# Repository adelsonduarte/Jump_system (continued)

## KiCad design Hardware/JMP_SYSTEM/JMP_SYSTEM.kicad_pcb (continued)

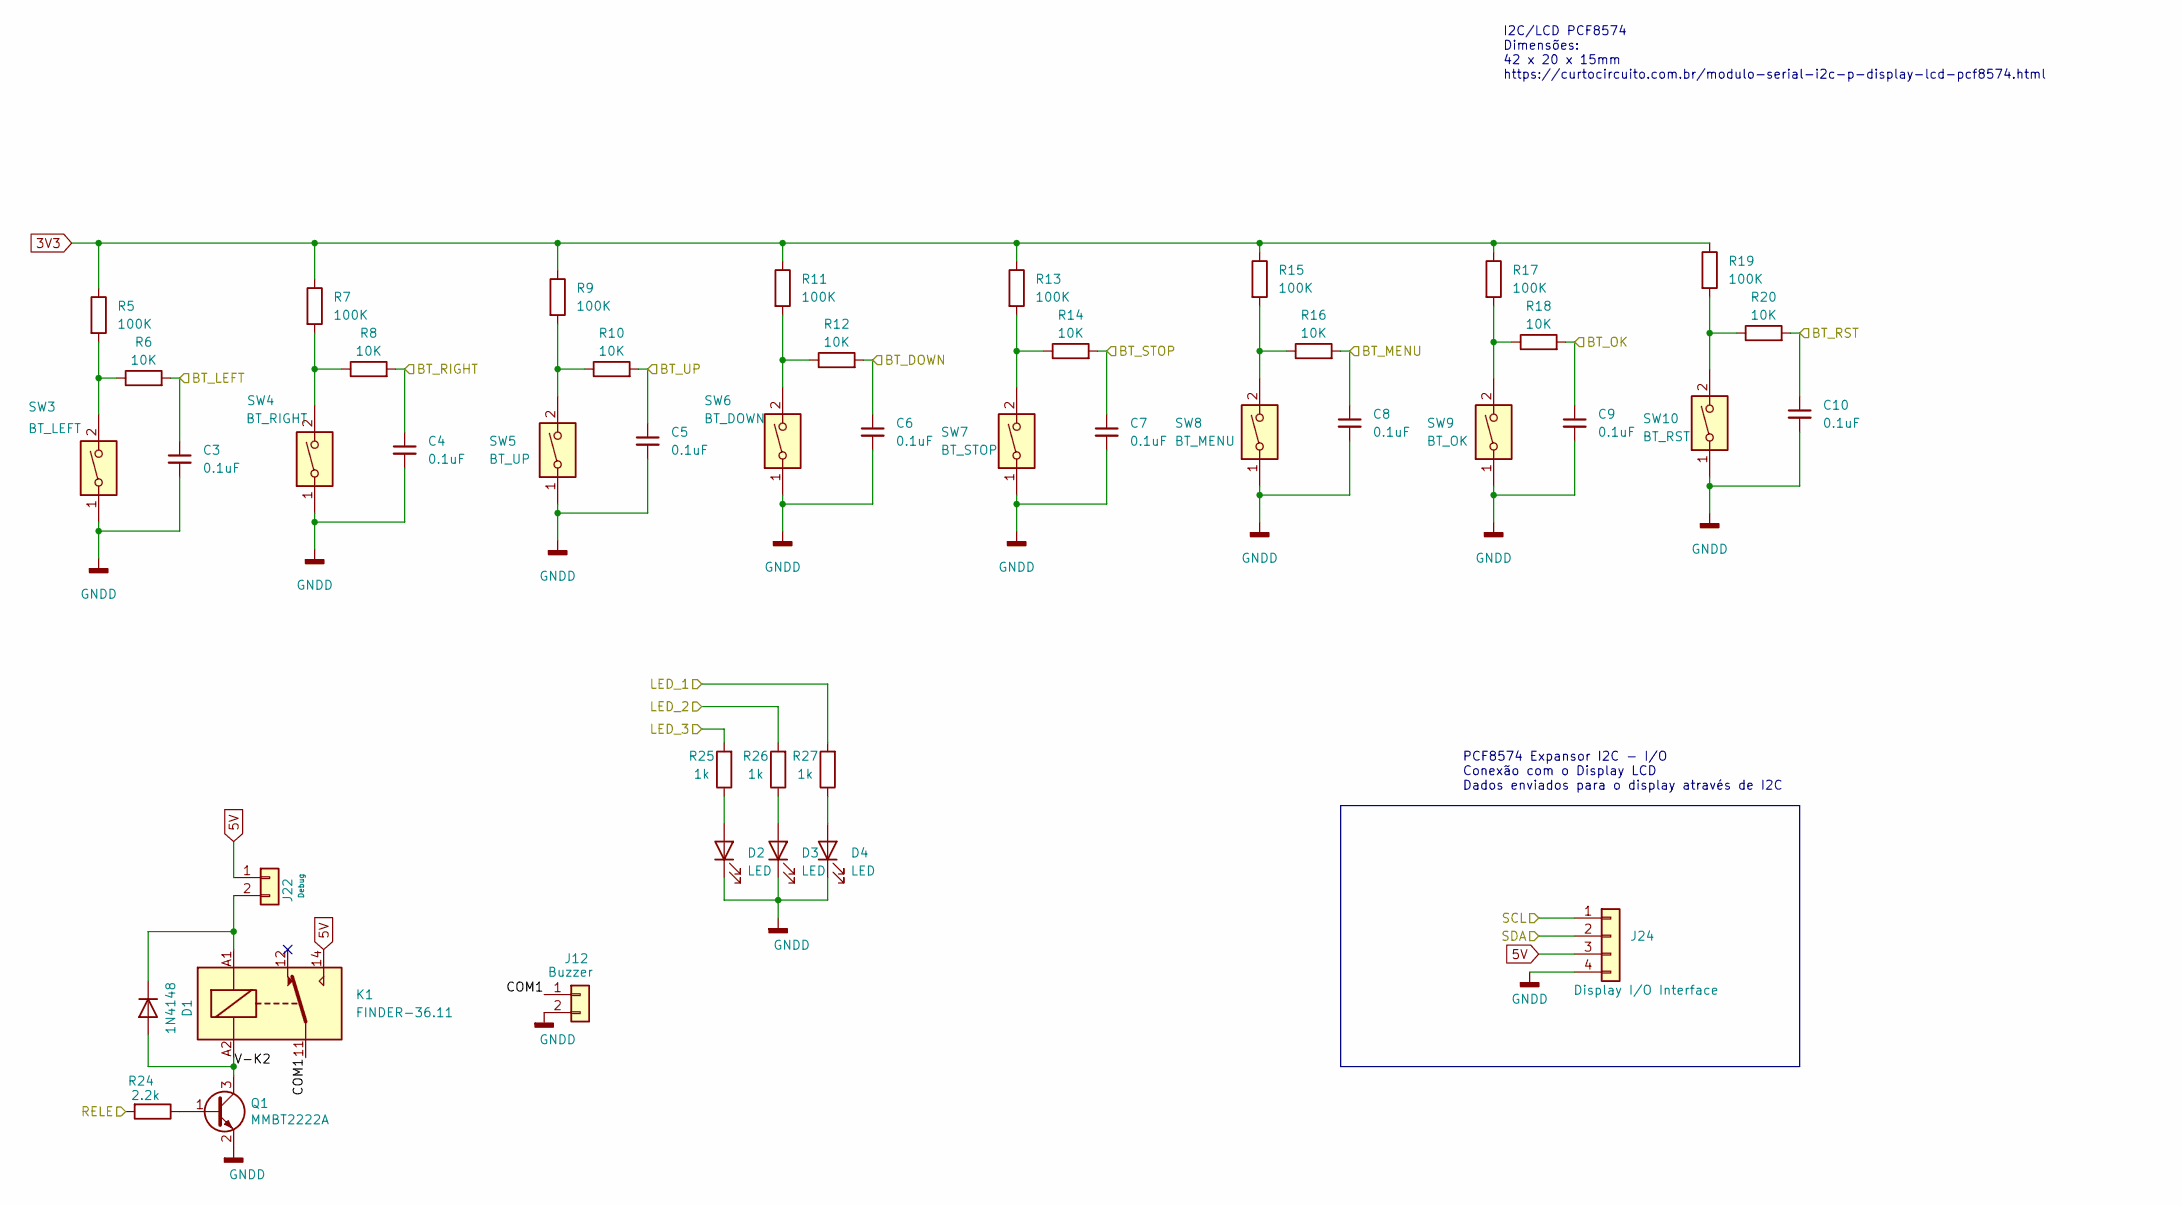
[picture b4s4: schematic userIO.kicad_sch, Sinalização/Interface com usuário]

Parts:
C3, C4, C5, C6, C7, C8, C9, C10: 0.1uF; R_0805_2012Metric_Pad1.20x1.40mm_HandSolder
D1: 1N4148; D_MiniMELF_Handsoldering
D2, D3, D4: LED; Molex_KK-254_AE-6410-02A_1x02_P2.54mm_Vertical
J12: Buzzer; Molex_KK-254_AE-6410-02A_1x02_P2.54mm_Vertical
J22: Debug; PinHeader_1x02_P2.54mm_Vertical
J24: Display I/O Interface; Molex_KK-254_AE-6410-04A_1x04_P2.54mm_Vertical
K1: FINDER-36.11; Relay_SPDT_Finder_36.11
Q1: MMBT2222A; SOT-23
R5, R7, R9, R11, R13, R15, R17, R19: 100K; R_0805_2012Metric_Pad1.20x1.40mm_HandSolder
R6, R8, R10, R12, R14, R16, R18, R20: 10K; R_0805_2012Metric_Pad1.20x1.40mm_HandSolder
R24: 2.2k; R_1206_3216Metric_Pad1.30x1.75mm_HandSolder
R25, R26, R27: 1k; R_0805_2012Metric_Pad1.20x1.40mm_HandSolder
SW3: BT_LEFT; Molex_KK-254_AE-6410-02A_1x02_P2.54mm_Vertical
SW4: BT_RIGHT; Molex_KK-254_AE-6410-02A_1x02_P2.54mm_Vertical
SW5: BT_UP; Molex_KK-254_AE-6410-02A_1x02_P2.54mm_Vertical
SW6: BT_DOWN; Molex_KK-254_AE-6410-02A_1x02_P2.54mm_Vertical
SW7: BT_STOP; Molex_KK-254_AE-6410-02A_1x02_P2.54mm_Vertical
SW8: BT_MENU; Molex_KK-254_AE-6410-02A_1x02_P2.54mm_Vertical
SW9: BT_OK; Molex_KK-254_AE-6410-02A_1x02_P2.54mm_Vertical
SW10: BT_RST; Molex_KK-254_AE-6410-02A_1x02_P2.54mm_Vertical

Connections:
3V3: R5.1, R7.1, R9.1, R11.1, R13.1, R15.1, R17.1, R19.1; also elsewhere on the board
5V: J22.1, J24.3, K1.14; also elsewhere on the board
/BT_DOWN: C6.1, R12.2; also elsewhere on the board
/BT_LEFT: C3.1, R6.2; also elsewhere on the board
/BT_MENU: C8.1, R16.2; also elsewhere on the board
/BT_OK: C9.1, R18.2; also elsewhere on the board
/BT_RIGHT: C4.1, R8.2; also elsewhere on the board
/BT_RST: C10.1, R20.2; also elsewhere on the board
/BT_STOP: C7.1, R14.2; also elsewhere on the board
/BT_UP: C5.1, R10.2; also elsewhere on the board
/LED_1: R27.2; also elsewhere on the board
/LED_2: R26.2; also elsewhere on the board
/LED_3: R25.2; also elsewhere on the board
/RELE: R24.2; also elsewhere on the board
/SCL: J24.1; also elsewhere on the board
/SDA: J24.2; also elsewhere on the board
/User _IO/COM1: J12.1, K1.11
/User _IO/V-K2: D1.2 (A), K1.A2, Q1.3 (C)
GNDA: C3.2, C4.2, C5.2, C6.2, C7.2, C8.2, C9.2, C10.2, D2.1 (K), D3.1 (K), D4.1 (K), J12.2, J24.4, Q1.2 (E), SW3.1, SW4.1, SW5.1, SW6.1, SW7.1, SW8.1, SW9.1, SW10.1; also elsewhere on the board
unnamed: D2.2 (A), R25.1
unnamed: D3.2 (A), R26.1
unnamed: D4.2 (A), R27.1
unnamed: D1.1 (K), J22.2, K1.A1
unnamed: Q1.1 (B), R24.1
unnamed: R5.2, R6.1, SW3.2
unnamed: R7.2, R8.1, SW4.2
unnamed: R9.2, R10.1, SW5.2
unnamed: R11.2, R12.1, SW6.2
unnamed: R13.2, R14.1, SW7.2
unnamed: R15.2, R16.1, SW8.2
unnamed: R17.2, R18.1, SW9.2
unnamed: R19.2, R20.1, SW10.2

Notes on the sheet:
PCF8574 Expansor I2C - I/O Conexão com o Display LCD Dados enviados para o display através de I2C
I2C/LCD PCF8574 Dimensões: 42 x 20 x 15mm https://curtocircuito.com.br/modulo-serial-i2c-p-display-lcd-pcf8574.html

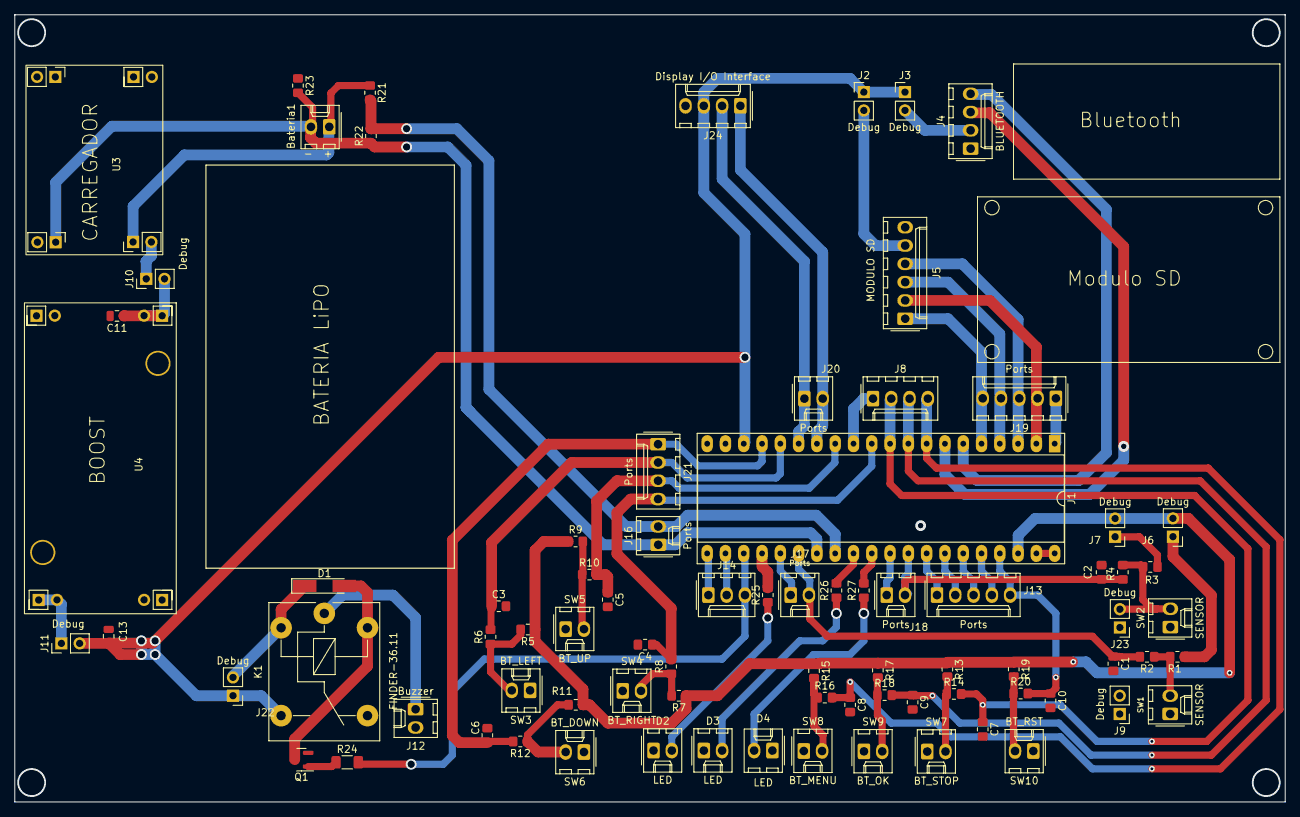
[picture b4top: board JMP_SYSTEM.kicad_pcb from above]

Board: 2 copper layers, 176.4 x 109.3 mm, 81 parts (0 on the bottom side), 60 nets.

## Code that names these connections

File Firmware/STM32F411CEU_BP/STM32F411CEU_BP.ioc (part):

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Mcu.Name=STM32F411C(C-E)Ux
Mcu.Package=UFQFPN48
Mcu.UserName=STM32F411CEUx
PA0-WKUP.Signal=S_TIM2_CH1_ETR
PA1.Signal=S_TIM2_CH2
PA10.GPIOParameters=GPIO_Label
PA10.GPIO_Label=LCD_D1
PA10.Signal=GPIO_Output
PA11.GPIOParameters=GPIO_Label
PA11.GPIO_Label=LCD_D0
PA11.Signal=GPIO_Output
PA12.GPIOParameters=GPIO_Label
PA12.GPIO_Label=LCD_EN
PA12.Signal=GPIO_Output
PA13.Mode=Serial_Wire
PA13.Signal=SYS_JTMS-SWDIO
PA14.Mode=Serial_Wire
PA14.Signal=SYS_JTCK-SWCLK
PA15.GPIOParameters=GPIO_Label
PA15.GPIO_Label=LCD_RW
PA15.Signal=GPIO_Output
PA2.Mode=Asynchronous
PA2.Signal=USART2_TX
PA3.Mode=Asynchronous
PA3.Signal=USART2_RX
PA4.GPIOParameters=GPIO_PuPd,GPIO_Label
PA4.GPIO_Label=SPI1_CS
PA4.GPIO_PuPd=GPIO_PULLUP
PA4.Signal=GPIO_Output
PA5.GPIOParameters=GPIO_PuPd
PA5.GPIO_PuPd=GPIO_PULLUP
PA5.Mode=Full_Duplex_Master
PA5.Signal=SPI1_SCK
PA6.GPIOParameters=GPIO_PuPd
PA6.GPIO_PuPd=GPIO_PULLUP
PA6.Mode=Full_Duplex_Master
PA6.Signal=SPI1_MISO
PA7.GPIOParameters=GPIO_PuPd
PA7.GPIO_PuPd=GPIO_PULLUP
PA7.Mode=Full_Duplex_Master
PA7.Signal=SPI1_MOSI
PA8.GPIOParameters=GPIO_Label
PA8.GPIO_Label=LCD_D3
PA8.Signal=GPIO_Output
PA9.GPIOParameters=GPIO_Label
PA9.GPIO_Label=LCD_D2
PA9.Signal=GPIO_Output
PB0.GPIOParameters=GPIO_PuPd,GPIO_Label,GPIO_ModeDefaultEXTI
PB0.GPIO_Label=BT_DOWN
PB0.GPIO_ModeDefaultEXTI=GPIO_MODE_IT_FALLING
PB0.GPIO_PuPd=GPIO_PULLUP
PB0.Signal=GPXTI0
PB1.GPIOParameters=GPIO_PuPd,GPIO_Label
PB1.GPIO_Label=BT_LEFT
PB1.GPIO_PuPd=GPIO_PULLUP
PB1.Signal=GPXTI1
PB12.GPIOParameters=GPIO_PuPd,GPIO_Label
PB12.GPIO_Label=LCD_D7
PB12.GPIO_PuPd=GPIO_NOPULL
PB12.Signal=GPIO_Output
PB13.GPIOParameters=GPIO_Label
PB13.GPIO_Label=LCD_D6
PB13.Signal=GPIO_Output
PB14.GPIOParameters=GPIO_Label
PB14.GPIO_Label=LCD_D5
PB14.Signal=GPIO_Output
PB15.GPIOParameters=GPIO_Label
PB15.GPIO_Label=LCD_D4
PB15.Signal=GPIO_Output
PB2.GPIOParameters=GPIO_PuPd,GPIO_Label
PB2.GPIO_Label=BT_ RIGHT
PB2.GPIO_PuPd=GPIO_PULLUP
PB2.Signal=GPXTI2
PB3.GPIOParameters=GPIO_Label
PB3.GPIO_Label=LCD_RS
PB3.Signal=GPIO_Output
PB4.GPIOParameters=GPIO_PuPd,GPIO_Label
PB4.GPIO_Label=BT_MENU
PB4.GPIO_PuPd=GPIO_PULLUP
PB4.Signal=GPXTI4
PB5.GPIOParameters=GPIO_PuPd,GPIO_Label,GPIO_ModeDefaultEXTI
PB5.GPIO_Label=BT_AVANCA
PB5.GPIO_ModeDefaultEXTI=GPIO_MODE_IT_FALLING
PB5.GPIO_PuPd=GPIO_PULLUP
PB5.Signal=GPXTI5
PB6.GPIOParameters=GPIO_PuPd,GPIO_Label,GPIO_ModeDefaultEXTI
PB6.GPIO_Label=BT_SELECT
PB6.GPIO_ModeDefaultEXTI=GPIO_MODE_IT_FALLING
PB6.GPIO_PuPd=GPIO_PULLUP
PB6.Signal=GPXTI6
PB7.GPIOParameters=GPIO_PuPd,GPIO_Label,GPIO_ModeDefaultEXTI
PB7.GPIO_Label=BT_STOP
PB7.GPIO_ModeDefaultEXTI=GPIO_MODE_IT_FALLING
PB7.GPIO_PuPd=GPIO_PULLUP
PB7.Signal=GPXTI7
PB8.GPIOParameters=GPIO_PuPd,GPIO_Label,GPIO_ModeDefaultEXTI
PB8.GPIO_Label=BT_INSERT
PB8.GPIO_ModeDefaultEXTI=GPIO_MODE_IT_FALLING
PB8.GPIO_PuPd=GPIO_PULLUP
PB8.Signal=GPXTI8
PC13-ANTI_TAMP.Signal=GPIO_Output
PH0\ -\ OSC_IN.Mode=HSE-External-Oscillator
PH0\ -\ OSC_IN.Signal=RCC_OSC_IN
PH1\ -\ OSC_OUT.Mode=HSE-External-Oscillator
PH1\ -\ OSC_OUT.Signal=RCC_OSC_OUT
RCC.HSE_VALUE=25000000
RCC.SYSCLKFreq_VALUE=100000000
RCC.SYSCLKSource=RCC_SYSCLKSOURCE_PLLCLK
board=custom

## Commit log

2022-07-28 Primeiro Commit
2022-08-08 Menus
2022-08-10 STM32
2022-08-12 10/08/22 - STM32
2022-08-16 new version
2022-08-18 jmpsys_higherlayer
2022-09-05 highLayer ok
2022-09-08 save txt -> ok
2022-09-12 FileIO ok
2022-09-26 sensor_bt_ok
2022-09-27 captura inicial de dados sensor
2022-10-03 sensor aquisition ok
2022-10-10 sensor working- BT
2022-10-24 UART OK, VERIFICAR MEMORIA SD
2022-10-27 Tentativa de reducao de codigo: Mexi no modulo de save, reading sensor e display, nao adiantou, faltando 4kB +-
2022-11-04 STARTING BLACKPILL SOLUTION
2022-12-01 cartao SD ok + Sensor
2022-12-06 versao 0.1
2022-12-15 v0.1 15/12/22 - ultima do ano
2023-01-11 upload do diretorio LCD+SENSOR/
2023-01-17 Firmware/LCD+SENSOR-> validacao da leitura do sensor
2023-01-31 Schematics and PCB layout
2023-02-03 Separacao do projeto em 3 PCBs - Core, PowerSupply, Display
2023-02-09 Roteamento considerando I2C e Display em conjunto. O display ficara suspenso. Adicionado molex em todos os conectores. Debugs sao pinos convencionais
2023-02-09 geracao de gebers
2023-02-09 geracao de gerbers
